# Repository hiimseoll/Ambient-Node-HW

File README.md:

# Ambient-Node-HW - Fan and Axis control

Seeeduino XIAO RP2040을 사용해 BLDC모터 와 스텝모터 2개를 이용해 얼굴 추적, 자동 회전, 자연풍, 수동 조작 기능을 구현한 Ambient node 하위 HW프로젝트

한림대학교 25년도 2학기 SW캡스톤디자인

## Demo & Hardware

| | | |
|:---:|:---:|:---:|
|  |  |  |
| pan 테스트1 | pan 테스트2 | tilt 테스트1 |
|  |  |  |
| pan-tilt 테스트1 | pan-tilt 테스트2 | fan 테스트1 |
|  |  |  |
| fan 테스트2 | fan 테스트3 | fan-pan-tilt 테스트 |
|  |  |  |
| 솔더링 플랜 | 솔더링 후 | 내부 구성 |

---

<p align="center">
  
</p>
<p align="center">프로젝트 데모 영상</p>

## 하드웨어 구성

- MCU: seeduino XIAO RP2040
  - 초기에는 Seeeduino XIAO SAMD21을 사용했으나, BLDC 선풍기 제어에 필요한 20~60kHz 대역 고주파 PWM을 안정적으로 출력하기 어려워 제어용 보드를 XIAO RP2040으로 변경
  - RP2040은 PWM 대역이 유연하여 BLDC 팬용 고주파 PWM 신호 발생에 적합

- 스텝모터 2축 구성  
  - 모터1 (PAN, 좌우)  
    - STEP: D1  
    - DIR: D10  
    - EN: D2 (HIGH = 비활성화, LOW = 활성화)  
    - 소프트웨어 위치 범위: -10000 ~ +10000 스텝
  - 모터2 (TILT, 상하)  
    - STEP: D4  
    - DIR: D3  
    - EN: D5 (HIGH = 비활성화, LOW = 활성화)  
    - 소프트웨어 위치 범위: 0 ~ 8500 스텝 (0 = HOME)

- BLDC 선풍기 구성 
  - PWM 제어: D8 사용. 약 30Khz 고주파 PWM을 출력하며 듀티를 조정해 속도를 제어
  - FG(홀 센서) 입력: D9 사용. 인터럽트로 펄스를 카운트하여 RPM 계산.

- 기타 인터페이스 구성 
  - Serial: USB 디버그 및 테스트 명령 수신에 사용. 
  - Serial1: 얼굴 인식/좌표 및 제어 명령 수신용 UART로 사용.

## 보드 변경 배경

- XIAO SAMD21 사용 시 제약사항 
  - 기본 PWM 주파수가 낮고 타이머/채널 제약이 존재하여 BLDC 팬이 요구하는 20~60kHz 고주파 PWM을 안정적으로 구현하기 어려움. 
  - 타이머 레지스터 직접 제어를 통해 이론상 수십 kHz PWM 생성은 가능하나, 시스템 타이머(millis, delay 등) 및 다른 기능과 충돌 가능성이 존재함.  
  - 여러 채널에서 동일한 주파수·해상도를 유지하기 어렵고, 실제 팬 구동 시 특정 구간에서 소음, 떨림, 불안정한 구동이 발생할 수 있음.

- XIAO RP2040 선택 이유
  - RP2040은 다수의 PWM 채널을 제공하며, 고주파 PWM을 안정적으로 생성할 수 있음.  
  - 본 프로젝트에서는 BLDC 팬 구동용 PWM을 20~60kHz 대역으로 설정하기 위해 보드를 XIAO RP2040으로 변경.
  - XIAO RP2040은 Seeeduino XIAO(SAMD21)와 동일한 핀아웃과 폼팩터를 가지므로, 기존 PCB 설계를 수정하지 않고 그대로 사용할 수 있음.  
  - 보드 변경 이후 BLDC, 스텝모터, 고속 시리얼 통신을 동시에 사용해도 전체 시스템이 안정적으로 동작함.

## 주요 기능

### 얼굴 추적(페이스 트래킹) 기능

- 얼굴 좌표를 Serial1로 수신하여 선풍기 헤드를 얼굴 방향으로 회전시키는 기능
- 카메라 해상도는 1920 x 1080 기준으로 동작
  
- 명령 형식(Serial1)
  - `P (x,y)` 형식을 사용
    - 예: `P (960,540)` 형태로 사용

- 동작 방식 
  - 입력된 x, y 좌표를 기준으로 PAN/TILT 목표 스텝(target_motor1_pos, target_motor2_pos)을 계산. 
  - P 제어와 딜레이 스무딩을 사용하여 모터 속도를 조정.
  - TRACKING_DEADZONE 범위 내에서는 출력 명령을 억제하여 중앙 부근에서의 미세 떨림을 방지.

- 추적 정지 방식 
  - `P X` 또는 `P x` 명령을 수신하면 페이스 트래킹이 비활성화됨.  
  - 스텝모터 EN 핀을 HIGH로 설정하여 전류를 차단하고, 모터2 현재 위치를 EEPROM에 저장.

### BLDC 풍속 제어 기능

- 고정 풍량 모드 
  - 명령 형식(Serial1): `S n` (0~5) 사용. 
    - 0: 정지 또는 최소 풍량 수준으로 동작.
    - 1~5: SPEED_LEVELS 테이블에 정의된 PWM 값으로 속도를 설정.

- 자연풍 모드
  - 명령 형식(Serial1):  
    - `N 1` : 자연풍 모드 활성화
    - `N 0` : 자연풍 모드 비활성화 
  - NATURAL_WIND_MIN_LEVEL ~ NATURAL_WIND_MAX_LEVEL 범위 내에서 풍속 레벨을 주기적으로 증감시키며 자연스러운 풍량 변화를 구현
  - setBldcSpeed()와 updateBldcSpeed()를 통해 targetBldcPwm까지 1씩 보간하여 목표 PWM으로 서서히 수렴하도록 구현

- FG 기반 RPM 측정
  - BLDC_FG_PIN 인터럽트에서 fgPulseCount를 증가시키는 방식으로 펄스를 카운트
  - FG 3펄스를 1회전으로 가정하여 1초마다 RPM을 계산

### 자동 왕복 회전 모드 (좌우 자동 스윙)

- 명령 형식(Serial1) 
  - `R 1` : 회전 모드 활성화
  - `R 0` : 회전 모드 비활성화

- 동작 방식
  - 모터1(PAN)을 MOTOR1_MIN_STEPS ~ MOTOR1_MAX_STEPS 범위 내에서 왕복 회전시키는 기능 
  - 한쪽 끝에 도달하면 ROTATION_PAUSE_MS 동안 정지 후 회전 방향을 반전
  - 회전 모드 활성화 시 얼굴 추적 및 수동 조작 모드는 자동으로 비활성화

### 수동 조작 모드 (리모컨/버튼 대응)

- 명령 형식(Serial1, `A d state`)  

  - 모터1 (좌우) 제어  
    - `A r 1` : 오른쪽으로 수동 이동 시작
    - `A r 0` : 오른쪽 이동 정지
    - `A l 1` : 왼쪽으로 수동 이동 시작
    - `A l 0` : 왼쪽 이동 정지

  - 모터2 (상하) 제어
    - `A u 1` : 위쪽으로 수동 이동 시작
    - `A u 0` : 위쪽 이동 정지
    - `A d 1` : 아래쪽으로 수동 이동 시작
    - `A d 0` : 아래쪽 이동 정지

- 특징
  - 수동 모드 진입 시 facetracking 및 rotation_mode 플래그를 자동으로 비활성화하여 수동 조작이 최우선으로 동작 
  - 각 모터는 소프트웨어 위치 제한(MIN/MAX/HOME)을 항상 체크하여 허용 범위 밖으로 이동하지 않도록 구현
  - 모터2는 수동 이동 후 motor2_needs_save 플래그를 설정하고, 일정 시간이 지난 후 EEPROM에 위치가 자동 저장

### 단발 테스트 이동 (USB Serial 전용)

- 명령 형식(USB Serial) 
  - `1 cw 1000`  
  - `2 ccw 500`

- 동작 방식
  - 입력 문자열에서 모터 번호, 방향(cw/ccw), 스텝 수를 파싱하여 test_motor1_steps, test_motor2_steps 변수에 기록
  - loop에서 driveTestMotors()를 통해 지정된 스텝 수만큼만 이동하도록 동작
  - 이동 중에도 MIN/MAX/HOME 위치 제한을 적용
  - 테스트 이동 종료 후 EN 핀을 HIGH로 설정하여 모터 전류를 차단

### 모터 전원 관리 및 위치 저장

- EN 핀 로직
  - EN = LOW : 모터 드라이버 활성화(전류 인가, 홀딩 토크 유지) 
  - EN = HIGH : 모터 드라이버 비활성화(전류 차단, 발열 감소)

- 자동 전원 OFF 기능  
  - 마지막 스텝 이후 ENABLE_OFF_DELAY_MS 이상 동작이 없을 경우 EN을 HIGH로 설정하여 모터 전류를 자동 차단  
  - 수동 조작, 테스트 이동, 회전 모드, 얼굴 추적이 모두 비활성화된 상태에서만 적용

- 모터2 위치 EEPROM 저장
  - motor2_position은 MotorPosition 구조체(위치 값 및 유효 플래그) 형태로 EEPROM에 저장
  - motor2_position 변경 시 motor2_needs_save 플래그가 설정
  - 마지막 이동 후 EEPROM_SAVE_DELAY_MS가 경과하면 savePositionToFlash()를 호출하여 자동 저장 
  - 부팅 시 EEPROM에서 데이터를 읽어 VALID_SIGNATURE를 확인하고, 유효 시 해당 위치로 복원되며, 유효하지 않을 경우 HOME(0)으로 초기화 후 저장

### 디버그 및 유틸리티 기능

- USB Serial (Serial)
  - 그래프 모드  
    - `graph` 명령으로 그래프 디버그 모드를 토글
    - 활성화 시 Serial1로 "Time,Target,Current" 포맷의 데이터를 주기적으로 출력  
  - EEPROM 유틸리티  
    - `clear` : motor2_position을 초기화하고 유효 플래그를 제거
    - `sethome` : 현재 motor2_position을 HOME(0)으로 설정하고 EEPROM에 저장

- UART (Serial1) 사용
  - 얼굴 좌표 및 모든 제어 명령을 Serial1로 수신
  - 버퍼에 여러 줄이 쌓인 경우 가장 마지막 유효 명령만 처리하도록 구현

## 제어 로직 요약

- 모터 제어 우선순위는 다음과 같음.
  1. 수동 모터 조작 (A …)  
  2. 단발 테스트 스텝 이동 (1/2 cw/ccw …)  
  3. 자동 왕복 회전 (R 1)  
  4. 얼굴 추적 (P (x,y))

- loop 처리 흐름
  - 각 프레임마다 processUartCommand(), processDebugCommand()를 호출하여 명령을 처리
  - 우선순위에 따라 driveManualMotors(), driveTestMotors(), rotationMode(), faceTrackingControl() 중 하나를 실행.
  - checkMotorPowerOff(), naturalWindMode(), updateBldcSpeed(), checkAutoSave()를 호출하여 전원 관리, 자연풍 모드, BLDC 속도 보정, EEPROM 저장을 수행.
  - BLDC가 구동 중인 경우 measureRPM() 함수로 RPM을 주기적으로 측정

## 빌드 및 사용 방법

- Arduino IDE 보드 설
  - 보드: Seeed XIAO RP2040 보드 패키지 선택(https://github.com/earlephilhower/arduino-pico/releases/download/global/package_rp2040_index.json)
  - 시리얼 속도:  
    - USB Serial(Serial): 921600 사용함.  
    - UART(Serial1): 921600 사용함.

- 배선 및 업로드 절차  
  - 핀 정의에 맞게 스텝모터 드라이버와 BLDC 모터를 XIAO RP2040에 연결
  - 스케치를 업로드한 후 USB Serial 및 Serial1을 통해 동작을 검증

### 테스트 예시

- USB Serial(PC)에서 테스트
  - `1 cw 500`  
  - `2 ccw 500`

- Serial1(외부 장치)에서 제어
  - 얼굴 좌표: `P (960,540)`  
  - 얼굴 추적 정지: `P X`  
  - 풍속 설정: `S 3`  
  - 자연풍 모드: `N 1`  
  - 회전 모드: `R 1`  
  - 수동 조작: `A r 1`, `A r 0`, `A u 1`, `A u 0` 등 사용

## 주의사항 및 팁

- EN 핀 HIGH가 비활성화(전류 차단) 상태이므로, 구동 중이 아닐 때 EN을 HIGH로 유지하면 모터 발열이 감소됨.  
- 얼굴 추적, 자동 회전, 수동 조작 모드는 동시에 동작하지 않도록 상호 배타적으로 설계됨.  
- 모터2는 틸트 각도를 유지하기 위해 EEPROM에 위치를 저장. EEPROM_SAVE_DELAY_MS를 통해 저장 간격을 조절하여 EEPROM 수명을 보호.

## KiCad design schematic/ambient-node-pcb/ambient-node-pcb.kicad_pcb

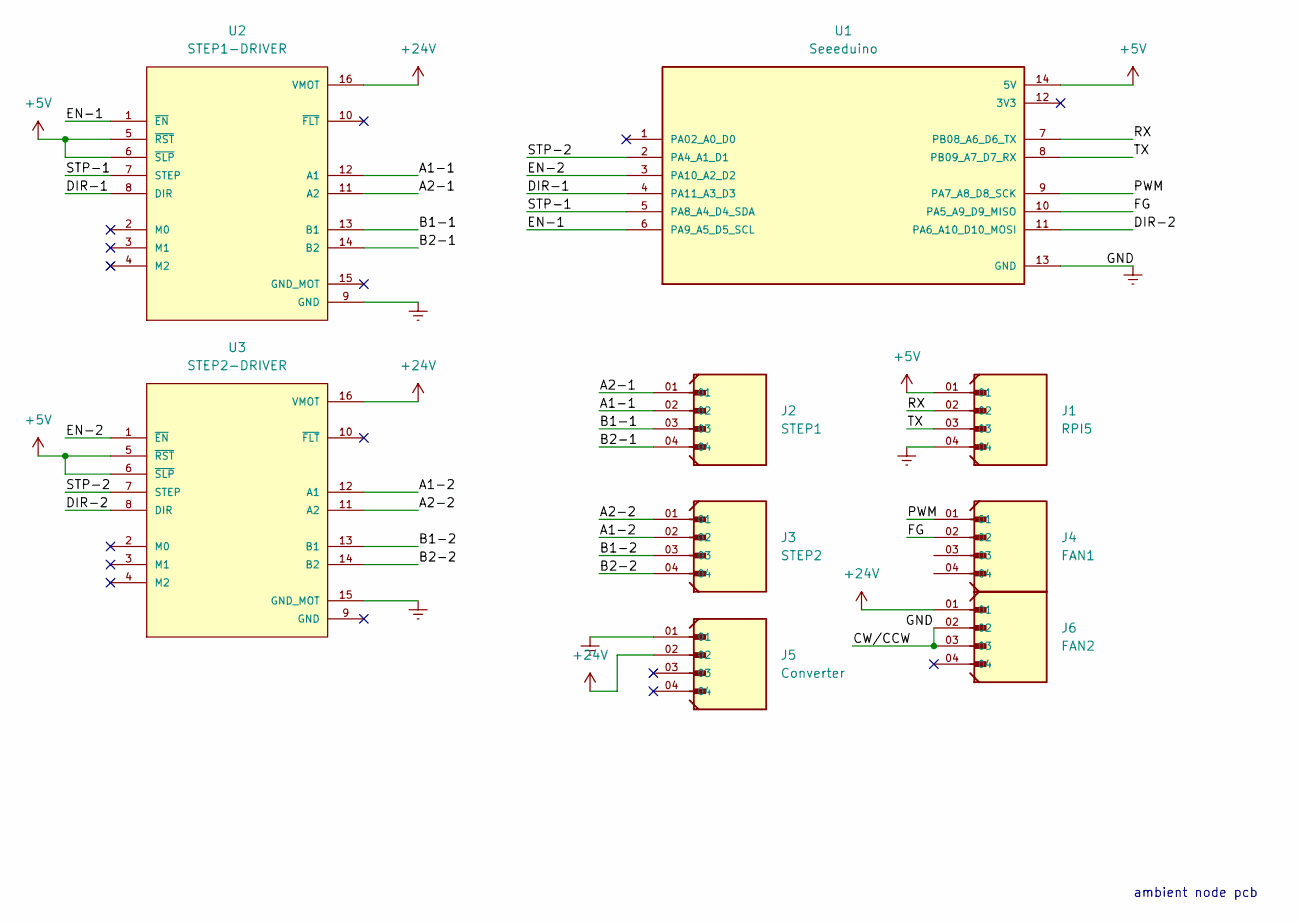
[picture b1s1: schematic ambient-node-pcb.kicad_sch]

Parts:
J1: RPI5; WURTH_61300411121
J2: STEP1; WURTH_61300411121
J3: STEP2; WURTH_61300411121
J4: FAN1; WURTH_61300411121
J5: Converter; WURTH_61300411121
J6: FAN2; WURTH_61300411121
U1: Seeeduino; MODULE_102010388; PARTREV N/A; DigiKey_Part_Number 1597-102010388-ND
U2: STEP1-DRIVER; IC_DRV8825_STEPPER_MOTOR_DRIVER_CARRIER
U3: STEP2-DRIVER; IC_DRV8825_STEPPER_MOTOR_DRIVER_CARRIER

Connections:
+5V: J1.01, U1.14 (5V), U2.5 (~RST), U2.6 (~SLP), U3.5 (~RST), U3.6 (~SLP)
+24V: J5.02, J6.01, U2.16 (VMOT), U3.16 (VMOT)
/A1-1: J2.02, U2.12 (A1)
/A1-2: J3.02, U3.12 (A1)
/A2-1: J2.01, U2.11 (A2)
/A2-2: J3.01, U3.11 (A2)
/B1-1: J2.03, U2.13 (B1)
/B1-2: J3.03, U3.13 (B1)
/B2-1: J2.04, U2.14 (B2)
/B2-2: J3.04, U3.14 (B2)
/DIR-1: U1.4 (PA11_A3_D3), U2.8 (DIR)
/DIR-2: U1.11 (PA6_A10_D10_MOSI), U3.8 (DIR)
/EN-1: U1.6 (PA9_A5_D5_SCL), U2.1 (~EN)
/EN-2: U1.3 (PA10_A2_D2), U3.1 (~EN)
/FG: J4.02, U1.10 (PA5_A9_D9_MISO)
/PWM: J4.01, U1.9 (PA7_A8_D8_SCK)
/RX: J1.02, U1.7 (PB08_A6_D6_TX)
/STP-1: U1.5 (PA8_A4_D4_SDA), U2.7 (STEP)
/STP-2: U1.2 (PA4_A1_D1), U3.7 (STEP)
/TX: J1.03, U1.8 (PB09_A7_D7_RX)
Earth: J1.04, J5.01, J6.02, J6.03, U1.13 (GND), U2.9 (GND), U3.15 (GND_MOT)

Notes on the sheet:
ambient node pcb

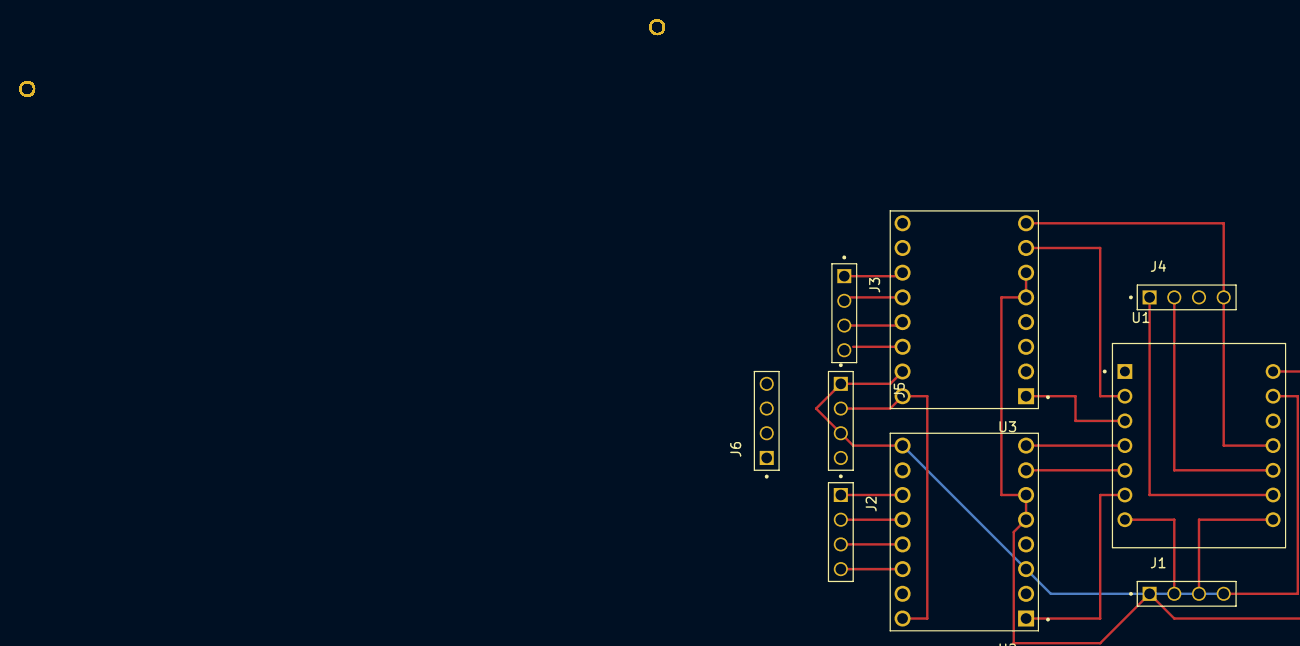
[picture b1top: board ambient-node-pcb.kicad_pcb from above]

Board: 2 copper layers, 9 parts (0 on the bottom side), 21 nets.

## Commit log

2025-12-02 Add test.txt with initial content 'schematic'
2025-12-02 ambient node pcb - schematic
2025-12-02 Update README with project details and instructions
    Added detailed project description, hardware configuration, features, and usage instructions for the Ambient-Node-HW project using the XIAO RP2040.
2025-12-02 Refine README content for clarity and conciseness
    Updated the README to improve clarity and remove redundant phrases.
2025-12-02 Add media/test.txt with initial content
2025-12-02 Rename before-soldering(plan).JPG to media/before-soldering(plan).JPG
2025-12-02 Rename internal-configuration.png to media/internal-configuration.png
2025-12-02 Rename pan-test2.gif to media/pan-test2.gif
2025-12-02 Rename pan-tilt-test1.gif to media/pan-tilt-test1.gif
2025-12-02 readme and media updated from forked repo
2025-12-02 demo video updated on readme
2025-12-11 final code upload
